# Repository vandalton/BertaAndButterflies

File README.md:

# Berta And Butterflies

> *TL;DR* If you just want to play the game, click [here](https://javatari.org/?ROM=https://github.com/vandalton/BertaAndButterflies/releases/download/v1.00/berta-and-butterflies.v1.00.ntsc.en.bin)
> 
> You can also see the demo on Youtube (in Polish): [https://www.youtube.com/shorts/mCUAv41lA1o?feature=share](https://www.youtube.com/shorts/mCUAv41lA1o?feature=share)

**Berta And Butterflies** is a game for Atari 2600 console.

It's a remake of the LCD game from the original ["Game & Watch"](https://nintendo.fandom.com/wiki/Egg) series from the '80. In Poland original Nintendo games were virtually unknown, but soviet clones made by [Elektronika](https://en.wikipedia.org/wiki/Elektronika) were very popular:

I wanted to write a game for Atari 2600. I know this console is extremely limited. On the other hand, this game is very simple, but still very enjoyable and fun. It looked like a good candidate to port it to Atari.

I replaced the character with my wife's Alice favorite stuffed toy from childhood - a small elephant called Berta.

| Original Berta | Digital Berta |
|----------------|---------------|
|||

As for 06 Jun 2024 the game is completed and I won't add any new features to the standard, 4KB version. Even if I wanted to, I have no spare place in the ROM - I can't even add one note more to the title music :)

The game's source file is in [software/atari2600-game](./software/atari2600-game/) folder. To compile it you'll need [batari Basic](https://github.com/batari-Basic/batari-Basic), however, you can download precompiled, binary version from the [releases](https://github.com/vandalton/BertaAndButterflies/releases/) page.

Besides the game, there are also three sub-projects within this repository:

1. A printed circut board design to create the simplest cartridge for any 4KB Atari 2600 game (**Berta And Butterflies** is also 4KB game) - [more details](./hardware/atari2600-simplest-cart/README.md).

2. Super Nintendo controller adapter, to control Berta in a different way than with a standard joystick - [more details](./hardware/snes-to-db9-controller-adapter/README.md).

3. Real Time Clock circuit design for Atari 2600, attachable to the second player's joystick port - [more details](./hardware/atari2600-rtc/README.md) (it is at experimental stage).

Although the game is completed, I'm going to develop it further and create 8KB version with RTC support - current time will be displayed on the title screen. That will make the game even more similiar to the original "Game & Watch" ;)

## How to play?

I recommend to play this game on a real console. It will work with any version, whether it is "Woody" from 1977, "Junior" from 80' or the most recent 2600+ from 2023.

If you have basic soldering skills, you can etch cartridge PCBs and make a real [cartridge](#cartridge). There will be also a limited run of physical cartridges released at some point in the near future. If you have a "universal" cartridge like Harmony or UnoCart, you can put the ROM there and load the game from it (however, these "universal" carts don't work with 2600+, as far as I know).

If you don't have Atari console, you can use emulator. There is plenty of Atari 2600 emulators to choose from:

1. [Javatari](https://javatari.org/?ROM=https://github.com/vandalton/BertaAndButterflies/releases/download/v1.00/berta-and-butterflies.v1.00.ntsc.en.bin) - an emulator that works in browser.
2. [Stella](https://stella-emu.github.io/) - probably the most well-known Atari 2600 emulator. There are versions for Windows, MacOS and Linux.
3. [Gopher2600](https://github.com/JetSetIlly/Gopher2600) - an emulator written in Go.

Just download the most recent ROM from [releases](https://github.com/vandalton/BertaAndButterflies/releases) page and load it in the emulator.

You can also use a device like Anbernic handheld with built-in Atari 2600 emulator (it uses Stella emulator internally):

While you are on the title screen, you can select difficulty level using console's difficulty switch (F4 in Javatari). The cloud is one of the level indicators. If it's over "B" letter it means "beginner", while "A" means "advanced". Another indicator is net's color - it is red in the advanced mode.

## Cartridge

Using elements from this repository and a few from outside it, you can make your own, real cartridge with the game. Only basic soldering skills are needed. You'll need:

- [Cartridge printed circuit board](./hardware/atari2600-simplest-cart/README.md) and a few electronic components, in particular a programmed EPROM memory.
- A case from [Sikor Soft](http://sikorsoft.waw.pl/hardware/obudowy-na-cartridge-2600-7800/).
- [Cover stickers](https://github.com/vandalton/BertaAndButterflies/releases/download/v1.00/cover.en.pdf). The PDF file has two layers. One layer contains everything that should be visible, and the second layer contains a pattern for cutting machines.

## History

I started this project to take part in [100 Commits](https://100commitow.pl/) competition.

Recently I was fascinated by Atari 2600 console and I wanted to write a program for it, which is allegedly very hard. This machine has only 128 bytes of RAM (it's not a mistake!) and has no graphics memory at all. There is even no such term as 'pixel'.

I want to check how hard it really is. I have no prior experience with 6502/6507 assembler, [batari Basic](https://github.com/batari-Basic/batari-Basic) etc. The competition motivates me to learn it :)

More details in [diary](./DIARY.md).

### Competition summary

Today (8 June 2024) is the last day of the competition. So much has happened during these 100 days! I've learned a lot and created a fully-fledged product - a game for Atari 2600 that one can play and find some joy in. I also met the requirement set by my wife - Berta’s character in the game had to be recognizable ;) Berta appeared on YouTube, on [Zero Page Homebrew](https://youtu.be/SA3xd5n5TF4?t=3413) and [DevMentors](https://youtu.be/TQQvmo6iMdc?t=1981) channels, as well as in an article on [AtariOnline](https://atarionline.pl/v01/index.php?subaction=showfull&id=1715228764&archive=&start_from=0&ucat=1&ct=nowinki). Despite a few moments of doubt caused by console's limitations, I completed the project. It wouldn’t have been possible without the help of many people. Alka_ja, Bartass, Kaziu, Milan Galcik, Sikor, x_angel - I thank you all! I’m also grateful for every star on GitHub, every test, and all the critical feedback. Even if I don’t make it to the finals, it was still worth it. The wealth of new experiences and skills is the most valuable reward. Although it would be great to add a sequel to this story!

And here is a sequel: "Berta and Butterflies" won the contest! I'm so happy! More details in the [diary](./DIARY.md#2024-06-29).

## How to contribute?

Many people helped me with this project, although not with means of GitHub pull-requests. Despite the standard version of the game won't change (it is already hardcoded on many cartridges), I have plenty of ideas for a possible future enhanced version. So, if you would like to help me, just fork this repo and create a pull-request - I'll review it.

Some of ideas:

- Support for real time clock (already in progress, you can see the time, but you can't set it).
- ROM size optimizations - I would love to fit the game together with RTC support in 4KB :)
- Two player mode (alternating).
- [SaveKey](https://atariage.com/store/index.php?l=product_detail&p=1194) support - although I don't find it very useful ;)
- Different color variations.
- Expanded title music.

## Would you like to create your own game for the Atari 2600?

Game programming itself is a challenge and provides a lot of satisfaction. Programming for the Atari 2600 is an even greater challenge, but the satisfaction is also much greater. The console’s limitations are enormous, and you need to think creatively to fit within them and create something playable. For example, in the case of Berta, even rendering a two-color, large character was quite difficult.

Players often asked me whether Berta could have an outline (she cannot), whether it could have eyes that aren't "holes" (she cannot), or whether butterflies could be different colors (they cannot). This should give you an idea of the scale of the console’s limitations.

In my experience, the following sources were invaluable:

- [batari Basic Commands](https://www.randomterrain.com/atari-2600-memories-batari-basic-commands.html#multikernel)
- Nick Montfort, Ian Bogost - [Racing the Beam](https://mitpress.mit.edu/9780262539760/racing-the-beam/).

I recommend starting with these two resources.

Note: Thinking about overcoming console limitations can be not only challenging but also addictive and dangerous! In the article [Brickbasher:How The Atari 2600 Almost Killed Me!](https://intotheverticalblank.com/2021/03/13/brickbasher-2600-wip/) the author describes his experiences related to creating a game for the Atari 2600. Once, he became so engrossed in his thoughts that he forgot he was driving, ran a red light, and almost caused an accident.

Fortunately, I haven’t experienced anything like that, but consider yourself warned!

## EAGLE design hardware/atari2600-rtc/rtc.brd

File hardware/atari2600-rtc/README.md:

# Real Time Clock for Atari 2600

In this folder you can find a design of an real time clock for Atari 2600.

Project files can be opened using Eagle. I don't provide gerber files at the moment, because the project is at experimental stage. However, the prototype works fine:

## The Idea

I designed this adapter primarily for my game - **Berta and Butterflies**. I wanted to make the game more similiar to the "Game & Watch" LCD game and display current time at title screen. It's a gadget, not a must have feature, but I'm determined to do it eventually.

<!-- ## Support the project

This design is open-source and you can download gerber files and order profesionally made PCBs from any manufacturer. However, you can order them from PCBWay: [https://www.pcbway.com/project/shareproject/SNES_controller_adapter_for_Atari_2600_DB9_a7f10165.html](https://www.pcbway.com/project/shareproject/SNES_controller_adapter_for_Atari_2600_DB9_a7f10165.html) - in this case I'll receive a few pennies, which will support this project or my other projects. Thanks! -->

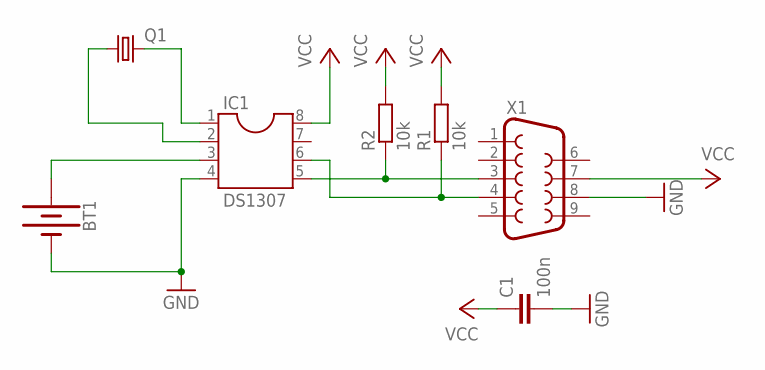
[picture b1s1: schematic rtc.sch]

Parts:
BT1: BATTERY-20MM_PTH; BATTCOM_20MM_PTH
C1: 100n; C025-025X050
IC1: DS1307; DIL08
Q1: CRYSTALTC26V; TC26V
R1, R2: 10k; 0204/7
X1: F09D

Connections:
GND: BT1.2 (-), C1.2, IC1.4, X1.8
unnamed: IC1.5, R2.1, X1.3
unnamed: IC1.6, R1.1, X1.4
unnamed: BT1.1 (+), IC1.3
unnamed: IC1.2, Q1.1
unnamed: IC1.1, Q1.2
VCC: C1.1, IC1.8, R1.2, R2.2, X1.7

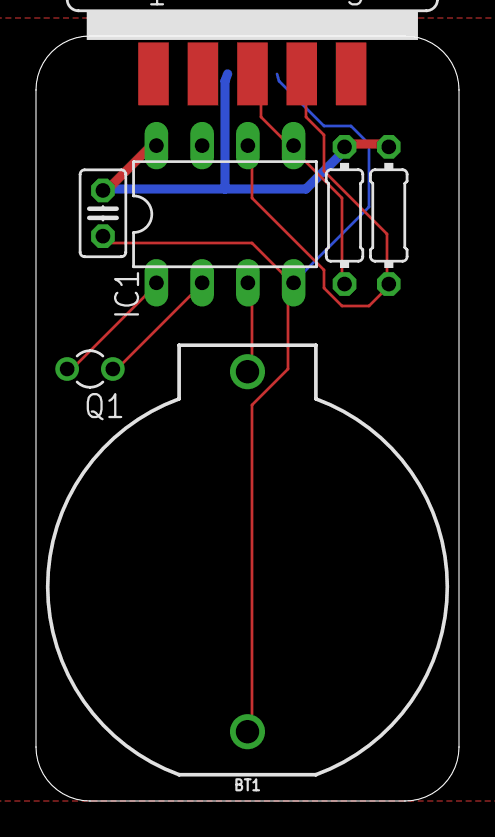
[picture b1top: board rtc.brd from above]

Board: 2 copper layers, 23.5 x 42.5 mm, 7 parts (0 on the bottom side), 7 nets.

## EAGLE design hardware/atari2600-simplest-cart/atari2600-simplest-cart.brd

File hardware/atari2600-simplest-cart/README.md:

# 4KB cartridge for Atari 2600

In this folder you can find a design of a cartridge for Atari 2600. It can store 4 kilobytes of data and was designed for "Berta and Butterflies" game, which is a 4KB game, but any game of this size will work.

Project files can be opened using Eagle. Gerber files, for ordering printed circut boards, are available here: [gerbers](https://github.com/vandalton/BertaAndButterflies/releases).

## The Idea

There is a lot of designs of cartridge PCBs for Atari 2600. Probably the most popular are these: [https://grandideastudio.com/portfolio/gaming/pixels-past/](https://grandideastudio.com/portfolio/gaming/pixels-past/). They are very good, reliable and battle tested. They need 74LS04 integrated circuit to work. It's an inverter. This particular IC has 6 gates and only one of these gates is used.

In my project I replaced IC with a inverter made of NPN transistor, two resistors and one capacitor. Total cost of these elements is half the price of 74LS04 IC. If you make one cartridge for your own needs, it doesn't make a difference, but if you make 50 of them, the difference is significant...

## Parts list

- **IC2** - 2732 EPROM
- **T1** - BC337 - NPN transistor (I also tested BC548B - it works)
- **R1** - 3,3 kOhm
- **R2** - 1 kOhm
- **C1** - 100nF
- **C2** - 1nF

## Support the project

This design is open-source and you can download gerber files and order profesionally made PCBs from any manufacturer. However, you can order them from PCBWay: [https://www.pcbway.com/project/shareproject/4KB_cartridge_for_Atari_2600_4b0ce5e2.html](https://www.pcbway.com/project/shareproject/4KB_cartridge_for_Atari_2600_4b0ce5e2.html) - in this case I'll receive a few pennies, which will support this project or my other projects. Thanks!

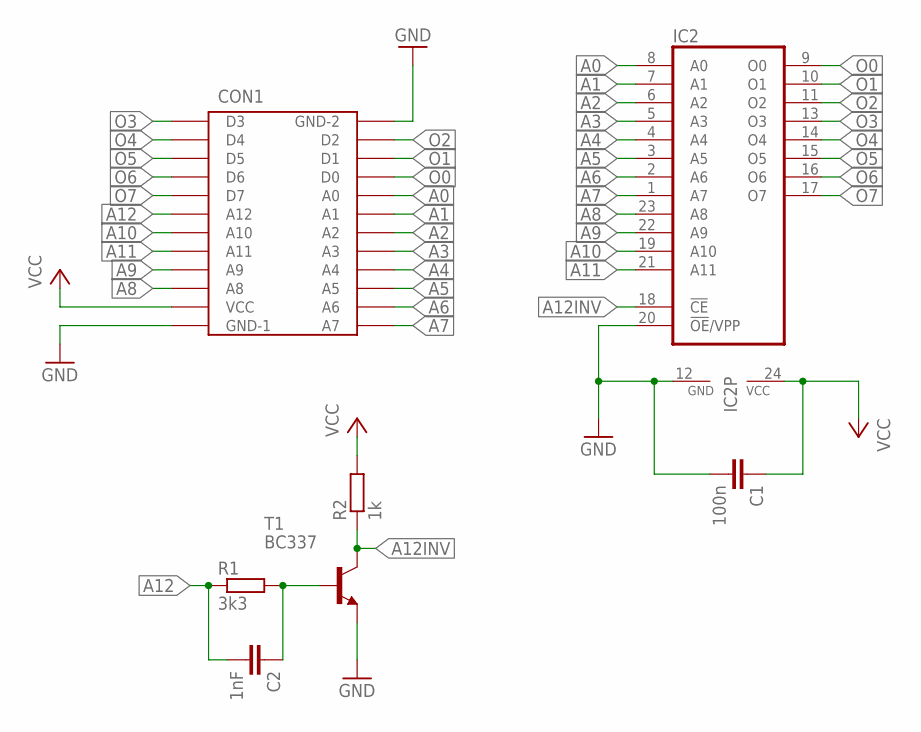
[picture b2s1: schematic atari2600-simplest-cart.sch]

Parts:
C1: 100n; C025-025X050
C2: 1nF; C025-025X050
CON1: 24PINEDGE-ATARI-2600
IC2: 2732; DIL24
R1: 3k3; 0204/7
R2: 1k; 0204/7
T1: BC337; TO92

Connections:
A0: CON1.20 (A0), IC2.8 (A0)
A1: CON1.19 (A1), IC2.7 (A1)
A2: CON1.18 (A2), IC2.6 (A2)
A3: CON1.17 (A3), IC2.5 (A3)
A4: CON1.16 (A4), IC2.4 (A4)
A5: CON1.15 (A5), IC2.3 (A5)
A6: CON1.14 (A6), IC2.2 (A6)
A7: CON1.13 (A7), IC2.1 (A7)
A8: CON1.10 (A8), IC2.23 (A8)
A9: CON1.9 (A9), IC2.22 (A9)
A10: CON1.7 (A10), IC2.19 (A10)
A11: CON1.8 (A11), IC2.21 (A11)
A12: C2.2, CON1.6 (A12), R1.1
A12INV: IC2.18 (!CE), R2.1, T1.3 (C)
GND: C1.2, CON1.12 (GND-1), CON1.24 (GND-2), IC2.12 (GND), IC2.20 (!OE!/VPP), T1.1 (E)
unnamed: C2.1, R1.2, T1.2 (B)
O0: CON1.21 (D0), IC2.9 (O0)
O1: CON1.22 (D1), IC2.10 (O1)
O2: CON1.23 (D2), IC2.11 (O2)
O3: CON1.1 (D3), IC2.13 (O3)
O4: CON1.2 (D4), IC2.14 (O4)
O5: CON1.3 (D5), IC2.15 (O5)
O6: CON1.4 (D6), IC2.16 (O6)
O7: CON1.5 (D7), IC2.17 (O7)
VCC: C1.1, CON1.11 (VCC), IC2.24 (VCC), R2.2

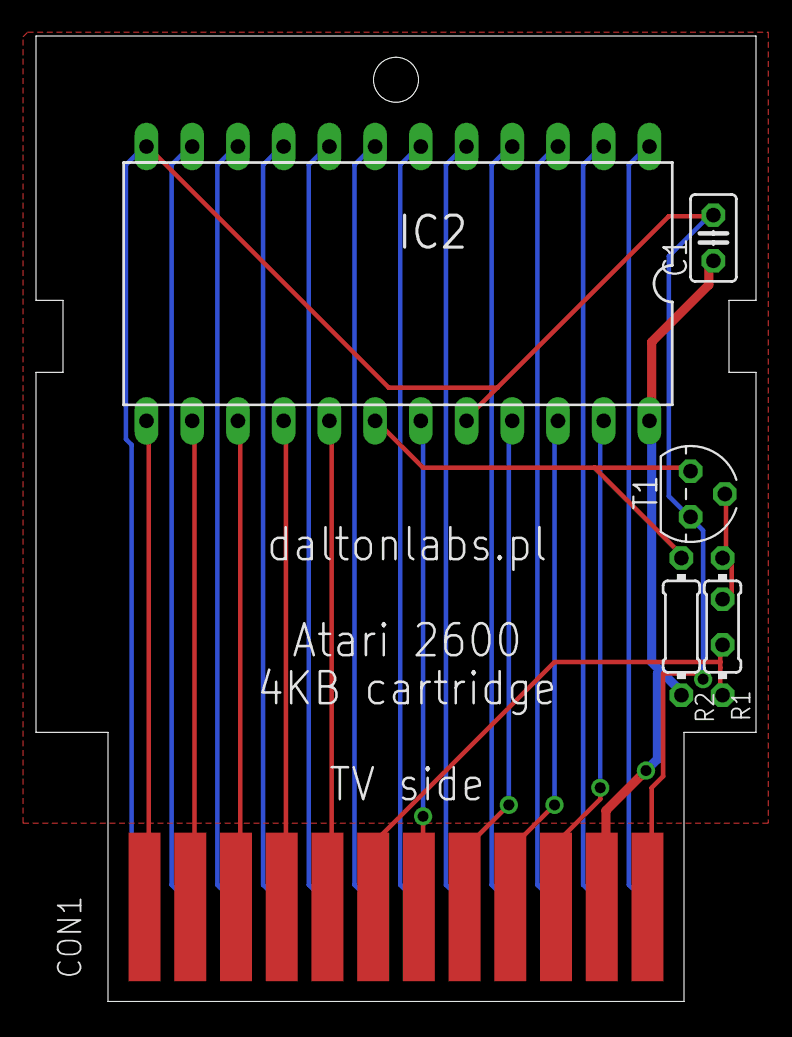
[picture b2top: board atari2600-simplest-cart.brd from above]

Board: 2 copper layers, 40.0 x 53.6 mm, 7 parts (1 on the bottom side), 25 nets.

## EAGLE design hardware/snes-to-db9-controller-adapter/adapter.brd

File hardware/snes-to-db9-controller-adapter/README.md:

# SNES controller adapter for Atari 2600

In this folder you can find a design of an adapter that allows to connect SNES compatible controller to Atari 2600.

Project files can be opened using Eagle. Gerber files, for ordering printed circut boards, are available here: [gerbers](https://github.com/vandalton/BertaAndButterflies/releases).

## The Idea

I designed this adapter primarily for my game - **Berta and Butterflies**. I wanted to make controlling experience more similiar to the "Game & Watch" consoles and be able to move the character to any corner using only one button:

However, the adapter has also a different mode. You can switch the mode by pressing Start+Select at the same time. In this mode it will work as a normal adapter. It means that the arrow keys will work as joystick directions and "Y" button as fire.

## Microprocessor

You need a programmed microprocessor for this project. You can use Atmega8, Atmega48 or Atmega88. Sources for microprocessor's program are available here: [snes-to-db9-controller-adapter](../../software/snes-to-db9-controller-adapter/), while the precompiled binaries are here: [releases](https://github.com/vandalton/BertaAndButterflies/releases).

You don't need to set any fuse bits - the default ones are ok (1MHz clock).

## Parts list

- **IC1** - Atmega8, Atmega48 or Atmega88 microprocessor
- **R1** - 10kOhm
- **C1** - 100nF
- **X1** - female DB9 connector
- **U1** - SNES controller socket

## Support the project

This design is open-source and you can download gerber files and order profesionally made PCBs from any manufacturer. However, you can order them from PCBWay: [https://www.pcbway.com/project/shareproject/SNES_controller_adapter_for_Atari_2600_DB9_a7f10165.html](https://www.pcbway.com/project/shareproject/SNES_controller_adapter_for_Atari_2600_DB9_a7f10165.html) - in this case I'll receive a few pennies, which will support this project or my other projects. Thanks!

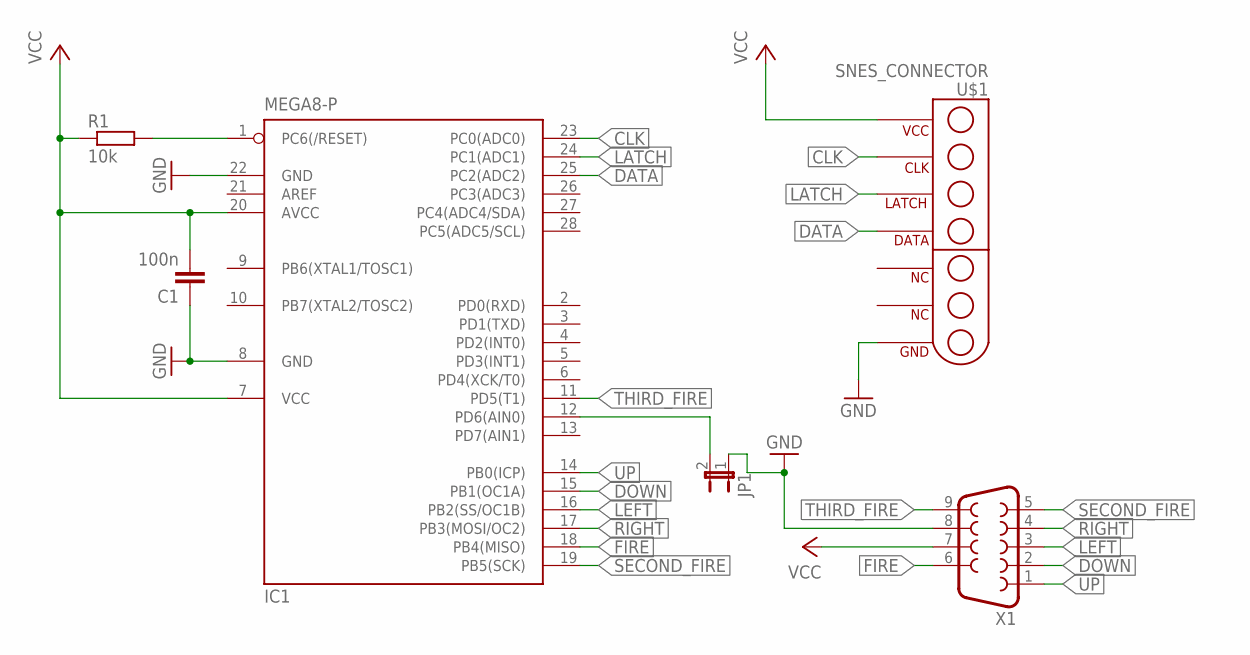
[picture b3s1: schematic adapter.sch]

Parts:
C1: 100n; C025-025X050
IC1: MEGA8-P; DIL28-3
JP1: JP1E; JP1
R1: 10k; 0207/10
U$1: SNES_CONNECTOR
X1: F09D

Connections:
CLK: IC1.23 (PC0(ADC0)), U$1.P$9 (CLK)
DATA: IC1.25 (PC2(ADC2)), U$1.P$11 (DATA)
DOWN: IC1.15 (PB1(OC1A)), X1.2
FIRE: IC1.18 (PB4(MISO)), X1.6
GND: C1.1, IC1.8 (GND), IC1.22 (GND), JP1.1, U$1.P$14 (GND), X1.8
LATCH: IC1.24 (PC1(ADC1)), U$1.P$10 (LATCH)
LEFT: IC1.16 (PB2(SS/OC1B)), X1.3
unnamed: IC1.12 (PD6(AIN0)), JP1.2
unnamed: IC1.1 (PC6(/RESET)), R1.2
RIGHT: IC1.17 (PB3(MOSI/OC2)), X1.4
SECOND_FIRE: IC1.19 (PB5(SCK)), X1.5
THIRD_FIRE: IC1.11 (PD5(T1)), X1.9
UP: IC1.14 (PB0(ICP)), X1.1
VCC: C1.2, IC1.7 (VCC), IC1.20 (AVCC), R1.1, U$1.P$8 (VCC), X1.7

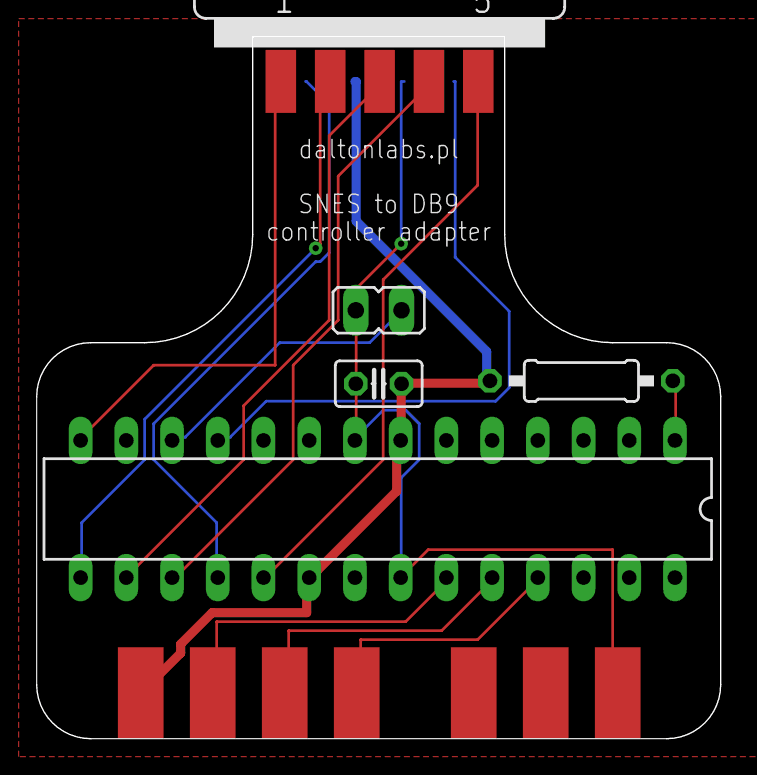
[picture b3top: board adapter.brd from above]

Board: 2 copper layers, 38.0 x 39.0 mm, 6 parts (0 on the bottom side), 14 nets.

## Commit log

2024-03-01 Add initial description
2024-03-01 Add documentation in Polish
2024-03-01 Fix typo in documentation
2024-03-01 Update documentation
2024-03-02 Update diary
2024-03-02 Add .gitignore
2024-03-02 Add first version of the cartridge PCB
2024-03-03 Add game code (it displays anything at the moment)
2024-03-03 Add preliminary design of player sprite
2024-03-04 Rename folder with static files
2024-03-04 Fix typo in diary
2024-03-04 Replace IC inverter with transistor based inverter on PCB
2024-03-04 Add playfild for experiments
2024-03-05 Add some tryouts with sprites and playfield
2024-03-05 Update documentation (reveal game idea)
2024-03-06 Add manual drawings/designs
2024-03-07 Update sprite designs
2024-03-07 Configure sprite and playfild to display Berta in a proper way
2024-03-08 Add experimental joystick handling
2024-03-09 Add butterfly net sprite
2024-03-10 Replace net sprite and move Berta when joystick moves
2024-03-10 Make butterfly net sprite wider
2024-03-11 Add experimental version of butterfly "animation"
2024-03-12 Remove unnecessary file
2024-03-13 Add experimental sound
2024-03-14 Add second butterfly
2024-03-14 Fix broken link in diary
2024-03-14 Add another butterflies
2024-03-15 Add net coloring when it catches butterfly
2024-03-15 Refactor the way Berta position is handled
2024-03-16 Add simple algorithm of butterfly releasing
2024-03-16 Correct butterflies releasing algorithm
2024-03-16 Add some Berta drawings (for cover)
2024-03-16 Move designs to separate folder
2024-03-17 Adjust NTSC colors and make NTSC version default
2024-03-18 Update cover designs
2024-03-18 Small correction in butterfly releasing algorithm
2024-03-19 Add SNES to DB9 adapter
2024-03-20 Update SNES to DB9 adapter
2024-03-22 Add possibility to catch butterfly
2024-03-22 Add logo and place it in readme
2024-03-23 Change max butterflies number dynamically
2024-03-24 Fix butterfly releasing algorithm
2024-03-27 Change folder structure to add software for microprocessor subprojects
2024-03-28 Add description to the snes to db9 adapter source file
2024-03-29 Update diary - add SNES prototype cable
2024-03-30 Update diary - experiments with the inverter
2024-03-30 Add behaviour after fail
2024-03-31 Fix in fail procedure
2024-03-31 Update diary - Happy Easter!
2024-04-03 Configure pins in SNES controller adapter
2024-04-03 Handle communication with SNES controller
2024-04-03 Fix typo in SNES controller adapter code
2024-04-04 Update diary - SNES adapter
2024-04-04 Update diary - cartridge works!
2024-04-05 Adjust SNES adapter for NES controller temporarly
2024-04-05 Update SNES controller adapter source
2024-04-06 Add missing capacitor to the cartridge board schematic
2024-04-06 Add missing capacitor to the cartridge board PCB
2024-04-07 Update diary - adapter boards ordered
2024-04-08 Add initial failing animation
2024-04-09 Update failing animation
2024-04-09 Add "game over" function
2024-04-10 Add acceleration of butterflies releasing
2024-04-11 Update diary - first Be(r)ta testers
2024-04-11 Add "title screen" and introduce arrays to save rom space
2024-04-12 Fix invalid loop
2024-04-12 Add mute option
2024-04-12 Adjust speed
2024-04-12 Move lives setting to the game starting routine
2024-04-13 Add title screen
2024-04-14 Add title music
2024-04-15 Slow down title music
2024-04-15 Add files to write high scores to the SaveKey device (but don't use it yet)
2024-04-16 Allow returning to the title screen after game over
2024-04-17 Add international title screen
2024-04-18 Differentiate difficulty levels on the title screen
2024-04-18 Adjust colors
2024-04-20 Fix bug with net coloring
2024-04-21 Update possible cover drawings
2024-04-22 Fix pin numbers in the SNES controller adapter code
2024-04-23 Add colorful cover draft
2024-04-24 Add "normal" mode in SNES controller adapter
2024-04-25 Eliminate some pfpixel calls to save ROM space
2024-04-26 Replace some pfpixel calls with direct playfield variables manipulation
2024-04-27 Update diary - Berta appeared in ZeroPage Homebrew stream!
2024-04-27 Bring pfpixels back
2024-04-28 Free up one variable
2024-04-28 Free up another variable
2024-04-28 Add high score saving
2024-04-28 Replace some playfield declarations to direct variables setting
2024-04-28 Fix butterflies limit calculation
2024-04-28 Change var44 usage to _temp to get rid of small artifact
2024-04-29 Refactor point scoreing
2024-04-29 Fix in butterflies limit calculation
2024-04-29 Adjust game difficulty
2024-05-01 Adjust difficulty
2024-05-02 Add some images generated by Leonardo AI
2024-05-02 Adjust fail animation
2024-05-02 Revert "Adjust fail animation"
    This reverts commit 136bc6e71f0fa15c2bb24f3fcfac7836dbfb52cf.
2024-05-04 Add game over sound signal
2024-05-06 Adjust real PAL timings
2024-05-07 Add another PAL timings
2024-05-08 Update diary - PAL timings
2024-05-08 Adjust PAL version difficulty
2024-05-08 Fix configuration jumper pin number in SNES controlleradapter
2024-05-09 Update diary - Berta on AtariOnline.pl!
2024-05-12 Change the way of controller adapter configuration
2024-05-13 Update diary - joystick configuration
2024-05-14 Add another drawing, redone by Leonardo AI
2024-05-15 Add some drawings redone by Leonardo AI
2024-05-18 Add Berta sketches
2024-05-18 Update diary - SaveKey
2024-05-20 Update daily - JUG meeting
2024-05-20 Update diary - RTC idea
2024-05-21 Add initial cover design
2024-05-21 Add International and Polish cartridge covers
2024-05-22 Update diary - covers
2024-05-25 Add draft version of RTC design
2024-05-26 Update RTC design
2024-05-27 Add covers with writings converted to paths
2024-05-28 Add PDF version of covers
2024-05-30 Change battery socket in RTC design
2024-05-31 Add cartridge documentation
2024-06-01 Update diary - I2C protocol
2024-06-01 Add files to support DS1307 RTC
2024-06-02 Update diary - RTC tryouts
2024-06-03 Update diary - RTC tryouts part II
2024-06-03 Update diary - vintage consoles fixed
2024-06-03 Update sample program for communicating with Ds1307 clock
2024-06-03 Add ground polygons to RTC board
2024-06-04 Update diary - RTC works!
2024-06-04 Update cartridge documentation
2024-06-04 Add a few images
2024-06-04 Add SNES controller adapter documentation
2024-06-04 Update readmes
2024-06-05 Update diary - final cartridge
2024-06-05 Add box front and back designs
2024-06-06 Rename Cover.pdf to cover.pdf
2024-06-06 Rename Cover.xcf to cover.xcf
2024-06-06 Rename Sprites.pdf to sprites.pdf
2024-06-06 Move RTC experiments to separate folder
2024-06-06 Add SNES controller adapter software documentation
2024-06-06 Add box designs in PDF format
2024-06-07 Shrink box back
2024-06-07 Update diary - box prototype
2024-06-07 Update readme - direct link to Javatari
2024-06-07 Update SNES controller adapter documentation
2024-06-07 Fix link in readme
2024-06-07 Fix a few typos in readme
2024-06-07 Update readme - competition summary
2024-06-08 Add RTC documentation
2024-06-08 Update RTC documentation
2024-06-08 Add RTC software documentation
2024-06-09 Update readme - how to play
2024-06-10 Add box back in English version
2024-06-20 Update box design PDFs
2024-06-20 Add box design with front and back together
2024-06-20 Update single file version of box design
2024-06-24 Add set time method in the RTC program
2024-06-25 Update diary - RTC setting
2024-07-03 Update diary - Berta is the winner!
2024-07-12 Fix typo in English box design
2024-07-15 Add missing english box designs
2024-07-15 Update single-file box designs
2024-07-15 Update PDF version of box designs
2024-07-18 Update diary - RTC pcbs
2024-11-25 Update diary - meetings, auctions
2024-11-28 First attempts to display digits on title screen
2024-11-28 Add another digits in the __draw_digit procedure
2024-11-30 Experiments with digits

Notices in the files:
parts and their libraries:
SparkFun-Batteries: Licensing: Creative Commons ShareAlike 4.0 International - https://creativecommons.org/licenses/by-sa/4.0
